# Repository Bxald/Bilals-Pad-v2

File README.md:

/>**Bilal’s MacroPad v2**  
It is my first ever engineering-related project and I think I did really good. It consists of 6 keys using Seeed XIAO RP2040 with a rotary encoder and custom built case.

It will be helping me making my time more efficient and help me in tasks that are very common but are taking too much time off my schedule + I can always change its code to program it the way I want.

**Features:** 

* 6 MX-style keys (in a 3×2 layout)  
* EC11 rotary encoder  
  (Rotate: Volume Up / Down  
  Press: Mute)  

* Direct GPIO wiring  
* Macro-ready firmware \- keys can be easily remapped  
* No RGB \- clean, simple, and functional (and maybe minimalistic)

**CAD Model:**  
The model is really simple, just using the simple guide. Top and bottom part held together with 4 M3 screws and headset inserts while having cut-outs for 6 switches and a rotary knob.

It has 2 separate printed parts, a bottom base that holds the pcb and everything on top while the top plate hides it all.

Made in Fusion360 (using it for the first time btw :\>).
**PCB:**  
Here is my PCB\! I made it myself in KiCad with the help of a tutorial at HackClub and some google too\! It is a 2 layered PCB board with through-hole XIAO RP2040, 6 switches and a rotary knob.

Schematic

PCB  
**Firmware:**  
This hackpad uses KMK firmware for everything, written in CircuitPython it can handle 6 keys functions (which is really easy to change, just edit it in keyboard.keymap in [main.py](http://main.py)), a rotary knob for volume up/down and pressing it down mutes the volume.

## **Bill of Materials (BOM)**

* 1× Seeed XIAO RP2040 (through-hole)  
* 6× MX-style mechanical switches  
* 6× Blank DSA keycaps (white)  
* 1× EC11 rotary encoder  
* 4× M3×16mm screws  
* 4× M3 heatset inserts  
* 1× 3D printed case (top \+ bottom)  
* Custom PCB (2-layer)  
* CircuitPython \+ KMK firmware

## **Notes**

* No RGB LEDs were used in this design.  
* All parts comply with the provided allowed materials list (by hackclub).  
* The project stays within all size and input limits.

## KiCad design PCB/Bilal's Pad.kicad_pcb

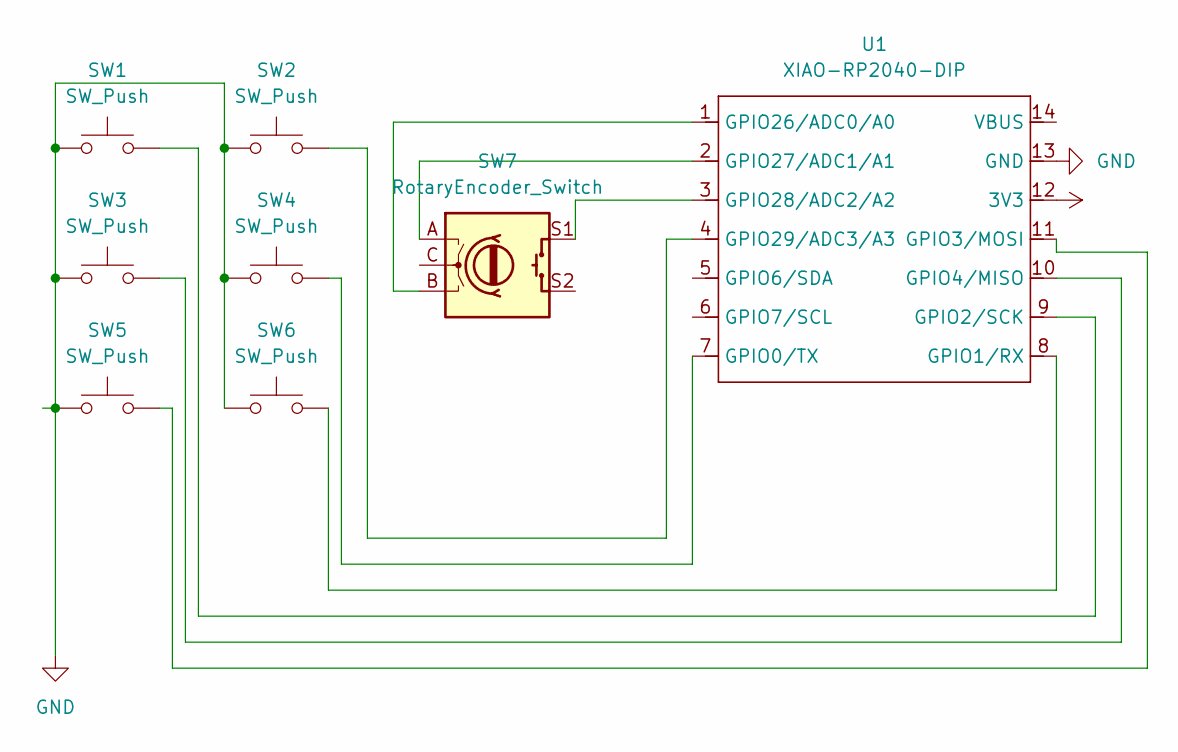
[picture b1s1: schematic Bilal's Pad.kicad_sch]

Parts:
SW1, SW2, SW3, SW4, SW5, SW6: SW_Push; SW_Cherry_MX_1.00u_PCB
SW7: RotaryEncoder_Switch; RotaryEncoder_Alps_EC11E-Switch_Vertical_H20mm
U1: XIAO-RP2040-DIP

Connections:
+3.3V: U1.12 (3V3)
GND: SW1.1, SW2.1, SW3.1, SW4.1, SW5.1, SW6.1, U1.13 (GND)
unnamed: SW4.2, U1.7 (GPIO0/TX)
unnamed: SW6.2, U1.8 (GPIO1/RX)
unnamed: SW1.2, U1.9 (GPIO2/SCK)
unnamed: SW5.2, U1.11 (GPIO3/MOSI)
unnamed: SW3.2, U1.10 (GPIO4/MISO)
unnamed: SW7.B, U1.1 (GPIO26/ADC0/A0)
unnamed: SW7.A, U1.2 (GPIO27/ADC1/A1)
unnamed: SW7.S1, U1.3 (GPIO28/ADC2/A2)
unnamed: SW2.2, U1.4 (GPIO29/ADC3/A3)

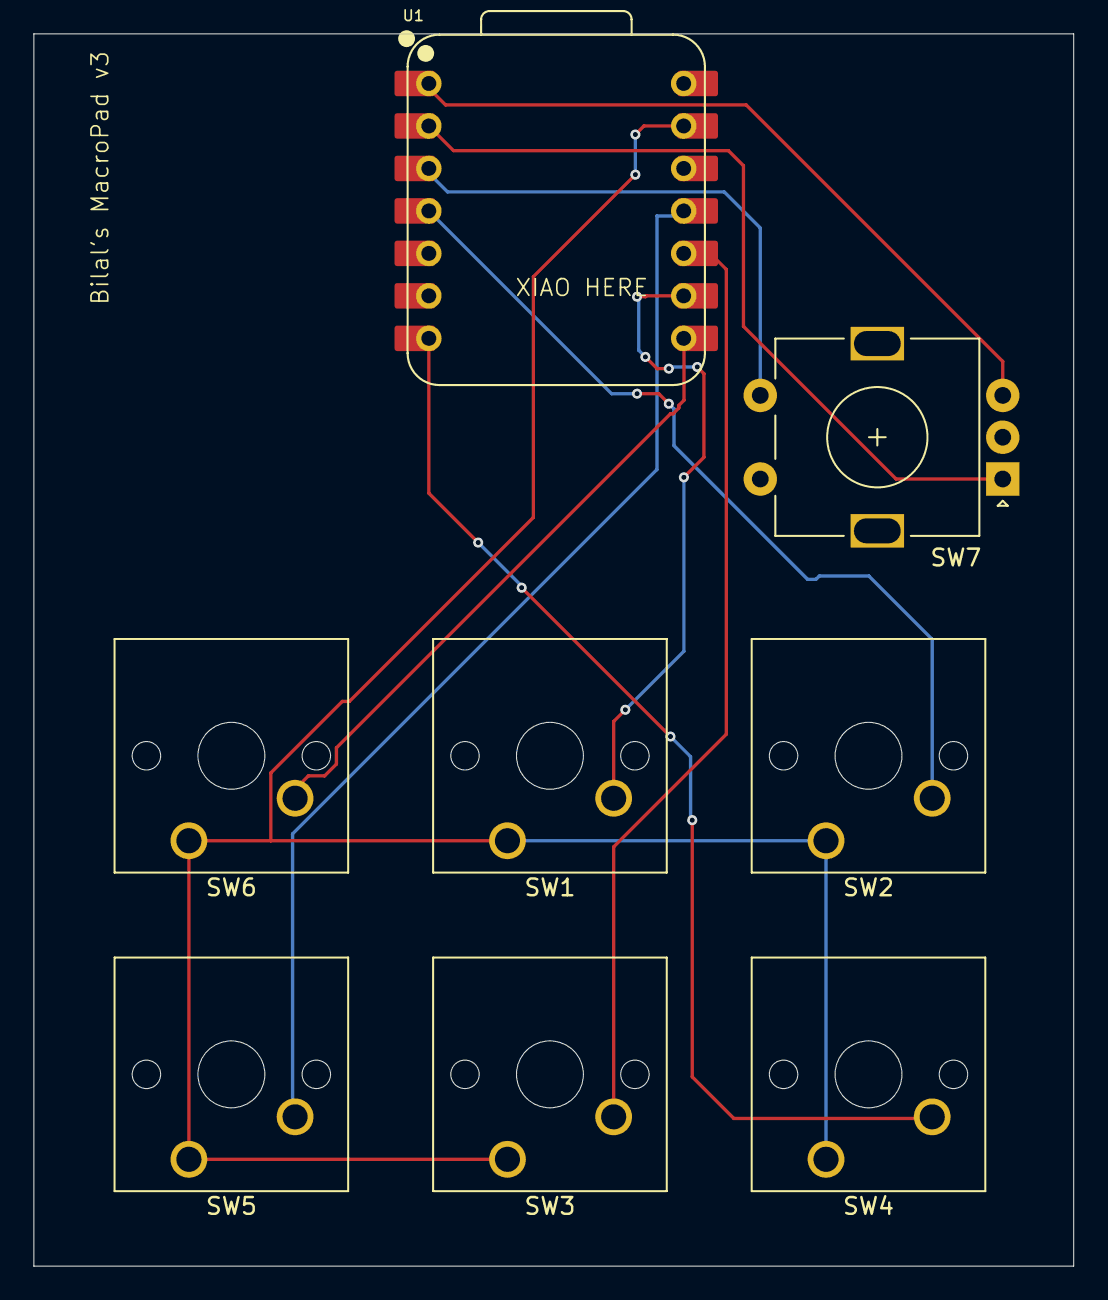
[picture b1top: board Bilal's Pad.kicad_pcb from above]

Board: 2 copper layers, 62.2 x 73.7 mm, 8 parts (0 on the bottom side), 10 nets.
